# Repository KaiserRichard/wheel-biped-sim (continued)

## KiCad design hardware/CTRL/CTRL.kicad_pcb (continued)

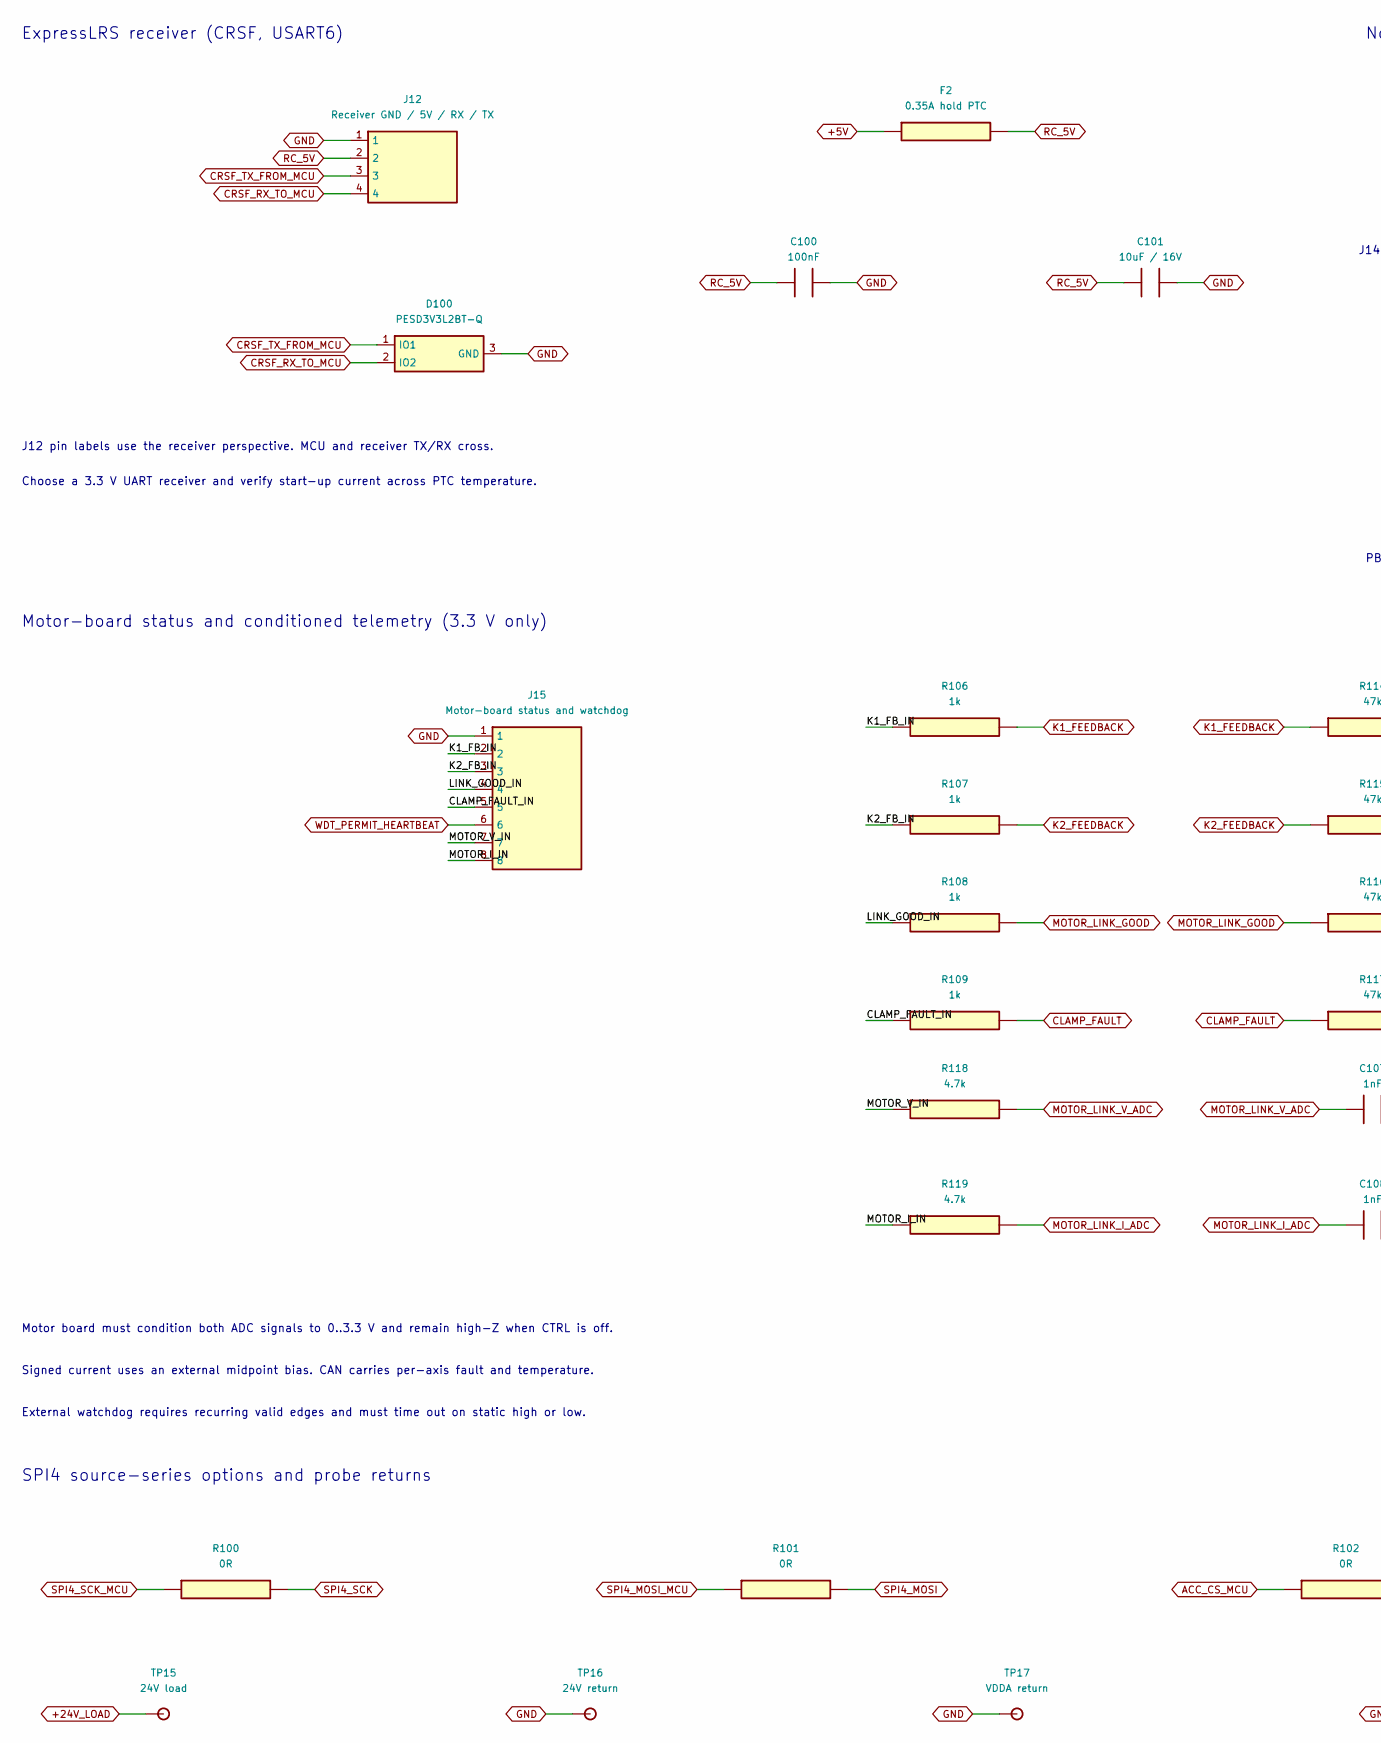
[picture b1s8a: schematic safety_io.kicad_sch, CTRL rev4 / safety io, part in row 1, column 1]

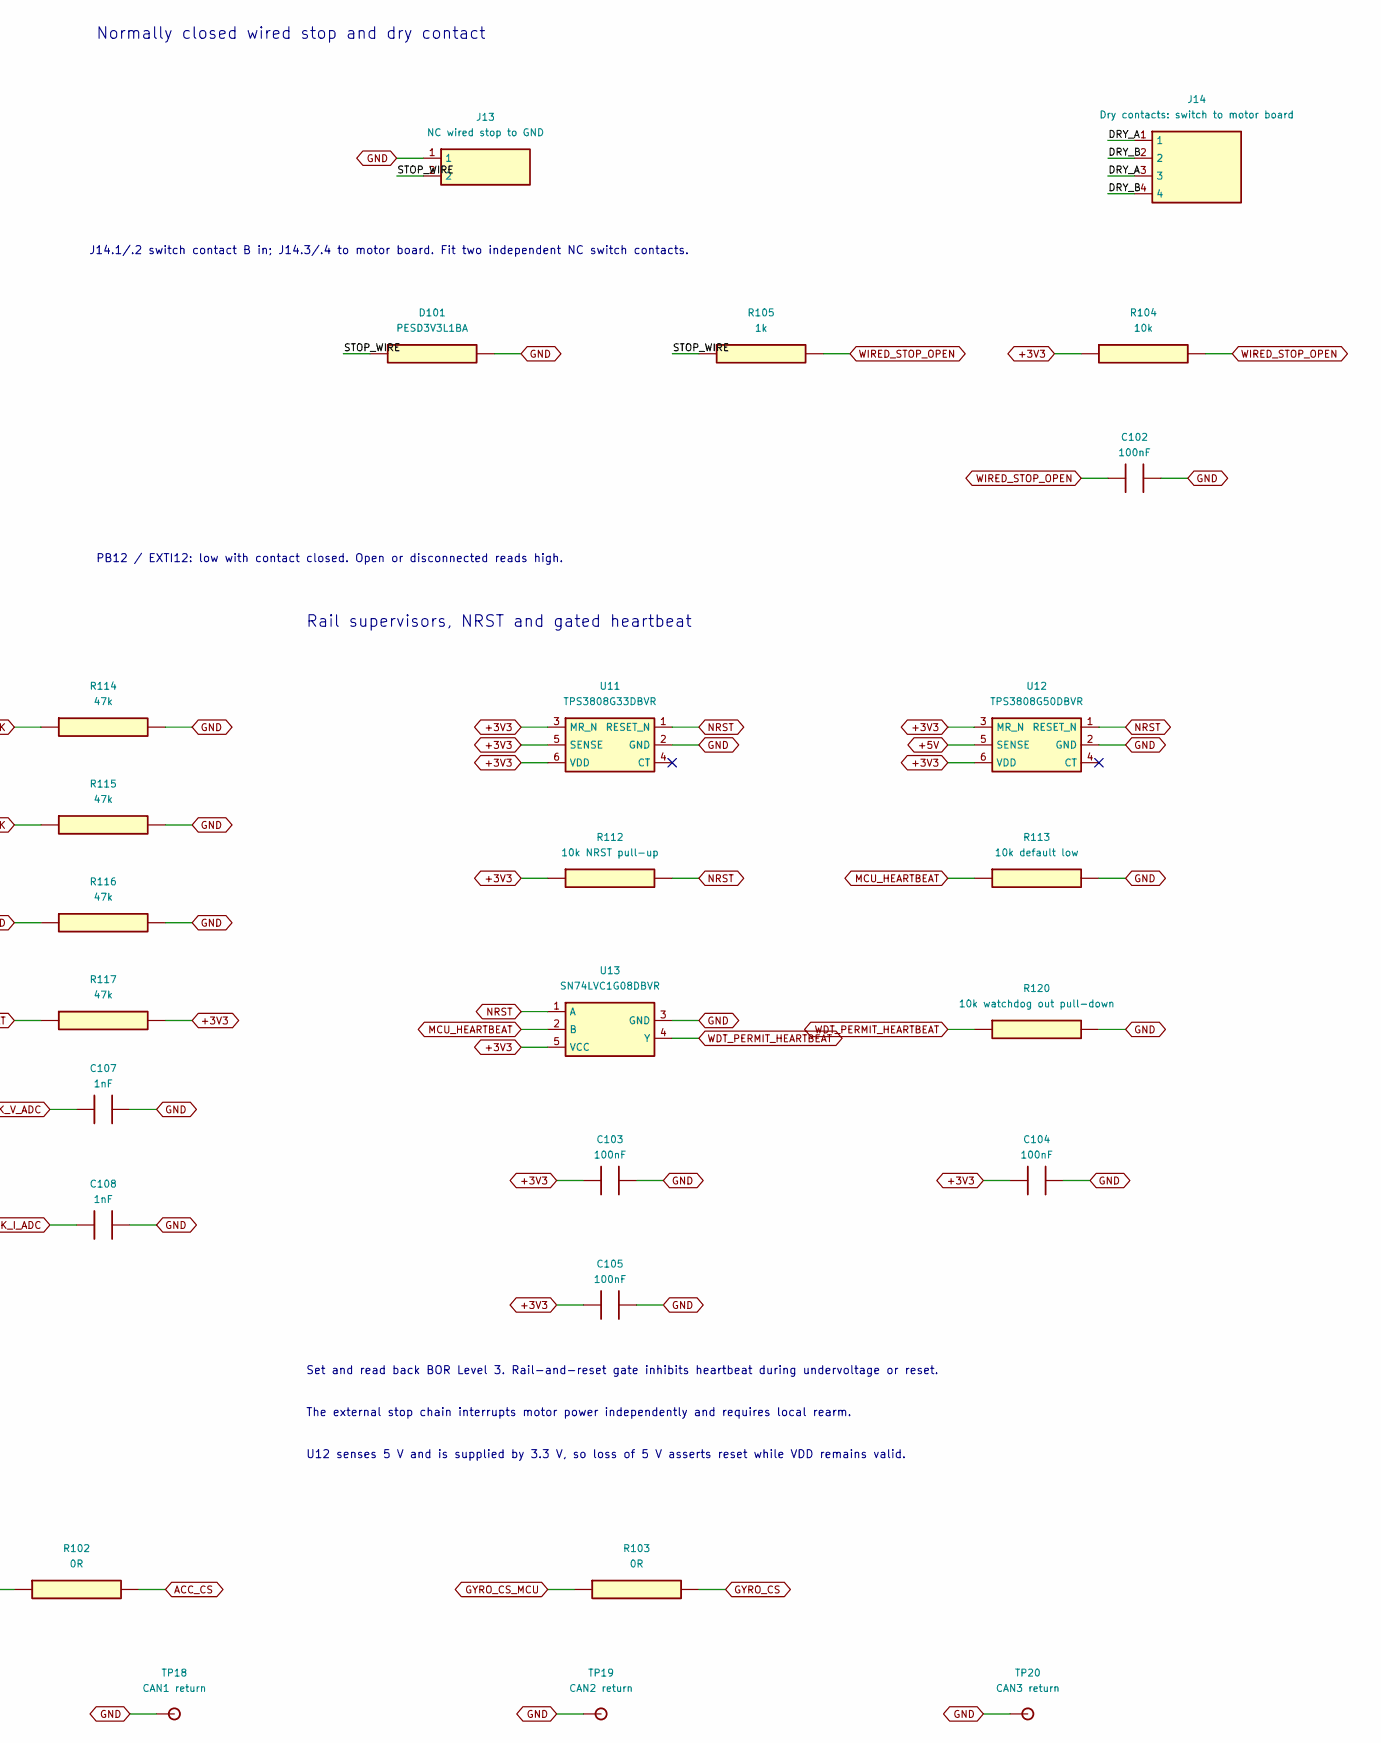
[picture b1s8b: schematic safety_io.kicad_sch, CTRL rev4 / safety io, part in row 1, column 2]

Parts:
C100, C102, C103, C104, C105: 100nF; C_0603_1608Metric
C101: 10uF / 16V; C_0805_2012Metric
C107, C108: 1nF; C_0603_1608Metric
D100: PESD3V3L2BT-Q; SOT-23
D101: PESD3V3L1BA; D_SOD-323
F2: 0.35A hold PTC; Fuse_1812_4532Metric; MPN MF-MSMF035/60X
J12: Receiver GND / 5V / RX / TX; JST_PH_B4B-PH-K_1x04_P2.00mm_Vertical
J13: NC wired stop to GND; Molex_Micro-Fit_3.0_43650-0215_1x02_P3.00mm_Vertical
J14: Dry contacts: switch to motor board; JST_PH_B4B-PH-K_1x04_P2.00mm_Vertical
J15: Motor-board status and watchdog; JST_PH_B8B-PH-K_1x08_P2.00mm_Vertical
R100, R101, R102, R103: 0R; R_0402_1005Metric
R104: 10k; R_0603_1608Metric
R105, R106, R107, R108, R109: 1k; R_0603_1608Metric
R112: 10k NRST pull-up; R_0603_1608Metric
R113: 10k default low; R_0603_1608Metric
R114, R115, R116, R117: 47k; R_0603_1608Metric
R118, R119: 4.7k; R_0603_1608Metric
R120: 10k watchdog out pull-down; R_0603_1608Metric
TP15: 24V load; TestPoint_Pad_D1.5mm
TP16: 24V return; TestPoint_Pad_D1.5mm
TP17: VDDA return; TestPoint_Pad_D1.5mm
TP18: CAN1 return; TestPoint_Pad_D1.5mm
TP19: CAN2 return; TestPoint_Pad_D1.5mm
TP20: CAN3 return; TestPoint_Pad_D1.5mm
U11: TPS3808G33DBVR; SOT-23-6
U12: TPS3808G50DBVR; SOT-23-6
U13: SN74LVC1G08DBVR; SOT-23-5

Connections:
+3V3: C103.1, C104.1, C105.1, R104.1, R112.1, R117.2, U11.3 (MR_N), U11.5 (SENSE), U11.6 (VDD), U12.3 (MR_N), U12.6 (VDD), U13.5 (VCC); also elsewhere on the board
+5V: F2.1, U12.5 (SENSE); also elsewhere on the board
+24V_LOAD: TP15.1; also elsewhere on the board
/Receiver, wired stop and motor-board interface/CLAMP_FAULT_IN: J15.5, R109.1
/Receiver, wired stop and motor-board interface/DRY_A: J14.1, J14.3
/Receiver, wired stop and motor-board interface/DRY_B: J14.2, J14.4
/Receiver, wired stop and motor-board interface/K1_FB_IN: J15.2, R106.1
/Receiver, wired stop and motor-board interface/K2_FB_IN: J15.3, R107.1
/Receiver, wired stop and motor-board interface/LINK_GOOD_IN: J15.4, R108.1
/Receiver, wired stop and motor-board interface/MOTOR_I_IN: J15.8, R119.1
/Receiver, wired stop and motor-board interface/MOTOR_V_IN: J15.7, R118.1
/Receiver, wired stop and motor-board interface/STOP_WIRE: D101.1, J13.2, R105.1
ACC_CS: R102.2; also elsewhere on the board
ACC_CS_MCU: R102.1; also elsewhere on the board
CLAMP_FAULT: R109.2, R117.1; also elsewhere on the board
CRSF_RX_TO_MCU: D100.2 (IO2), J12.4; also elsewhere on the board
CRSF_TX_FROM_MCU: D100.1 (IO1), J12.3; also elsewhere on the board
GND: C100.2, C101.2, C102.2, C103.2, C104.2, C105.2, C107.2, C108.2, D100.3 (GND), D101.2, J12.1, J13.1, J15.1, R113.2, R114.2, R115.2, R116.2, R120.2, TP16.1, TP17.1, TP18.1, TP19.1, TP20.1, U11.2 (GND), U12.2 (GND), U13.3 (GND); also elsewhere on the board
GYRO_CS: R103.2; also elsewhere on the board
GYRO_CS_MCU: R103.1; also elsewhere on the board
K1_FEEDBACK: R106.2, R114.1; also elsewhere on the board
K2_FEEDBACK: R107.2, R115.1; also elsewhere on the board
MCU_HEARTBEAT: R113.1, U13.2 (B); also elsewhere on the board
MOTOR_LINK_GOOD: R108.2, R116.1; also elsewhere on the board
MOTOR_LINK_I_ADC: C108.1, R119.2; also elsewhere on the board
MOTOR_LINK_V_ADC: C107.1, R118.2; also elsewhere on the board
NRST: R112.2, U11.1 (RESET_N), U12.1 (RESET_N), U13.1 (A); also elsewhere on the board
RC_5V: C100.1, C101.1, F2.2, J12.2
SPI4_MOSI: R101.2; also elsewhere on the board
SPI4_MOSI_MCU: R101.1; also elsewhere on the board
SPI4_SCK: R100.2; also elsewhere on the board
SPI4_SCK_MCU: R100.1; also elsewhere on the board
WDT_PERMIT_HEARTBEAT: J15.6, R120.1, U13.4 (Y)
WIRED_STOP_OPEN: C102.1, R104.2, R105.2; also elsewhere on the board

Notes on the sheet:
ExpressLRS receiver (CRSF, USART6)
J12 pin labels use the receiver perspective. MCU and receiver TX/RX cross.
Choose a 3.3 V UART receiver and verify start-up current across PTC temperature.
Normally closed wired stop and dry contact
J14.1/.2 switch contact B in; J14.3/.4 to motor board. Fit two independent NC switch contacts.
PB12 / EXTI12: low with contact closed. Open or disconnected reads high.
Motor-board status and conditioned telemetry (3.3 V only)
Motor board must condition both ADC signals to 0..3.3 V and remain high-Z when CTRL is off.
Signed current uses an external midpoint bias. CAN carries per-axis fault and temperature.
External watchdog requires recurring valid edges and must time out on static high or low.
Rail supervisors, NRST and gated heartbeat
Set and read back BOR Level 3. Rail-and-reset gate inhibits heartbeat during undervoltage or reset.
The external stop chain interrupts motor power independently and requires local rearm.
SPI4 source-series options and probe returns
U12 senses 5 V and is supplied by 3.3 V, so loss of 5 V asserts reset while VDD remains valid.

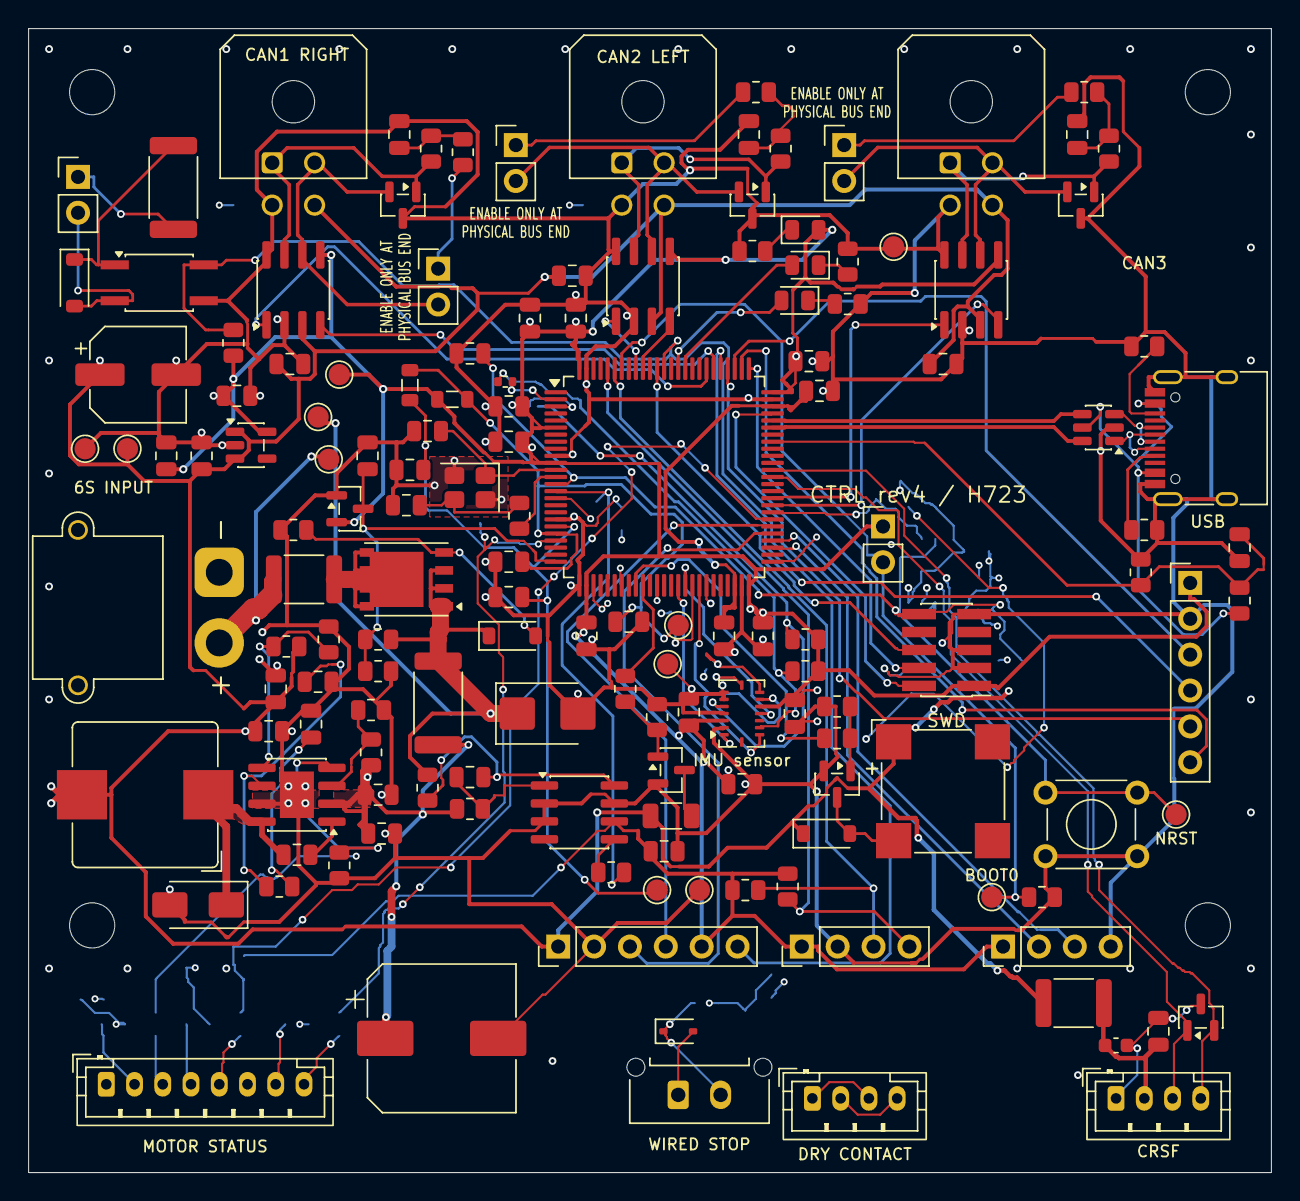
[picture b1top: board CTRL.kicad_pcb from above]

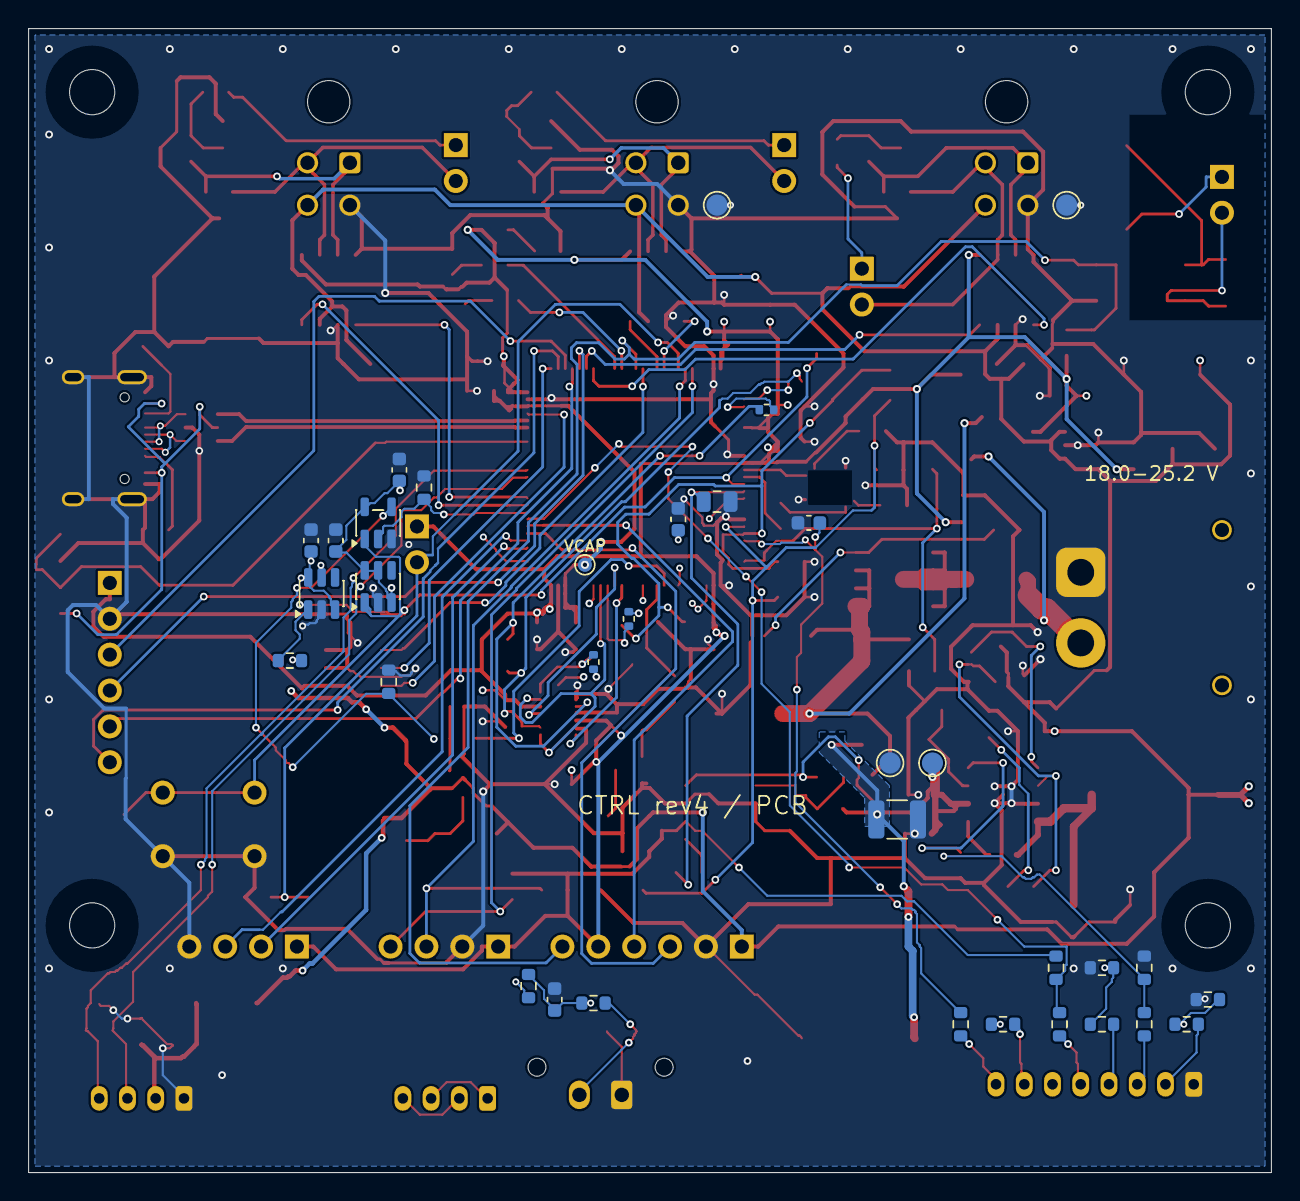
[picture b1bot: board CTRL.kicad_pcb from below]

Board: 4 copper layers, 88.0 x 81.0 mm, 187 parts (34 on the bottom side), 114 nets.

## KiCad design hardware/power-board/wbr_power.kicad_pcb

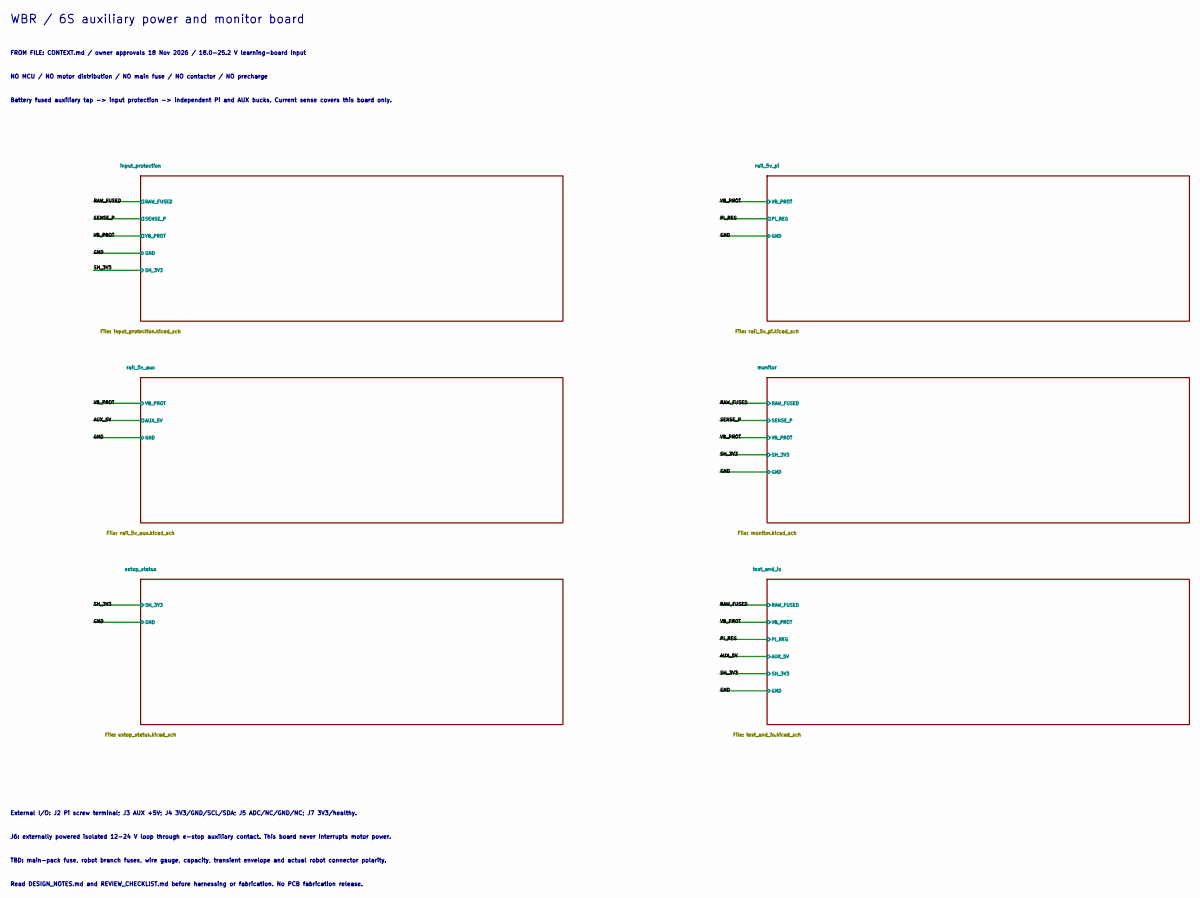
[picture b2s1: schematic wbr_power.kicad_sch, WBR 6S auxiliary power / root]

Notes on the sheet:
WBR / 6S auxiliary power and monitor board
FROM FILE: CONTEXT.md / owner approvals 18 Nov 2026 / 18.0-25.2 V learning-board input
NO MCU / NO motor distribution / NO main fuse / NO contactor / NO precharge
Battery fused auxiliary tap -> input protection -> independent Pi and AUX bucks. Current sense covers this board only.
External I/O: J2 Pi screw terminal; J3 AUX +5V; J4 3V3/GND/SCL/SDA; J5 ADC/NC/GND/NC; J7 3V3/healthy.
J6: externally powered isolated 12-24 V loop through e-stop auxiliary contact. This board never interrupts motor power.
TBD: main-pack fuse, robot branch fuses, wire gauge, capacity, transient envelope and actual robot connector polarity.
Read DESIGN_NOTES.md and REVIEW_CHECKLIST.md before harnessing or fabrication. No PCB fabrication release.
